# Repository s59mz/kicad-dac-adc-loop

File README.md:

# dac_adc_pmod
PMOD PCB module with LTC2627 (I2C-DAC) and LTC2402 (SPI-ADC) loopback

Schematic:
[dac_adc_pmod.pdf](dac_adc_pmod.pdf)

BOM:
[dac_adc_pmod.csv](dac_adc_pmod.csv)

Gerbers:
[gerbers.zip](https://github.com/s59mz/kicad-dac-adc-loop/raw/main/gerbers.zip)

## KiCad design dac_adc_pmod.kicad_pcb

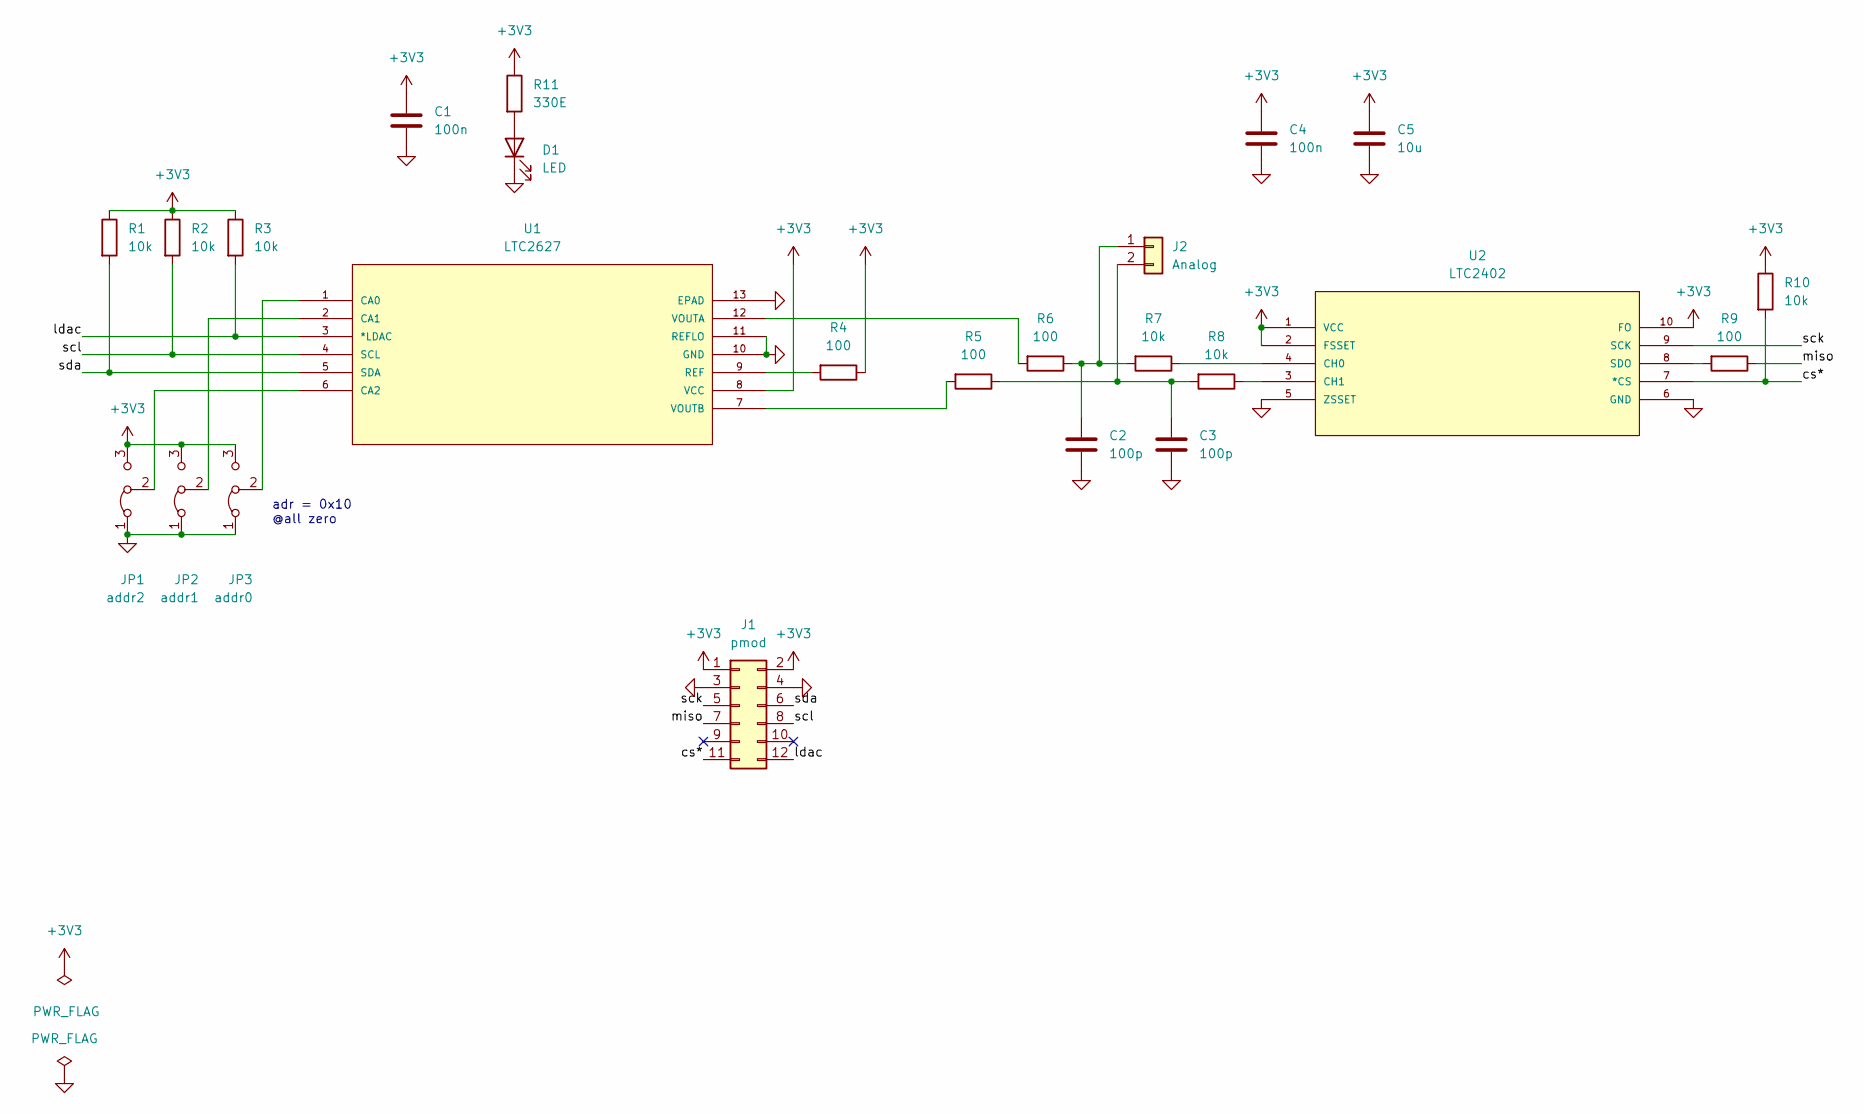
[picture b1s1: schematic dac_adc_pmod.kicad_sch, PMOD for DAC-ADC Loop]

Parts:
C1, C4: 100n; C_0603_1608Metric_Pad1.08x0.95mm_HandSolder
C2, C3: 100p; C_0603_1608Metric_Pad1.08x0.95mm_HandSolder
C5: 10u; C_0603_1608Metric_Pad1.08x0.95mm_HandSolder
D1: LED; LED_0603_1608Metric_Pad1.05x0.95mm_HandSolder
J1: pmod; PinHeader_2x06_P2.54mm_Horizontal
J2: Analog; PinHeader_1x02_P2.54mm_Vertical
JP1: addr2; PinHeader_1x03_P2.54mm_Vertical
JP2: addr1; PinHeader_1x03_P2.54mm_Vertical
JP3: addr0; PinHeader_1x03_P2.54mm_Vertical
R1, R2, R3, R7, R8, R10: 10k; R_0603_1608Metric_Pad0.98x0.95mm_HandSolder
R4, R5, R6, R9: 100; R_0603_1608Metric_Pad0.98x0.95mm_HandSolder
R11: 330E; R_0603_1608Metric_Pad0.98x0.95mm_HandSolder
U1: LTC2627; DFN-12; MANUFACTURER_PART_NUMBER ltc2627cde
U2: LTC2402; MSOP-10; MANUFACTURER_PART_NUMBER ltc2402ims

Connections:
+3V3: C1.1, C4.1, C5.1, J1.1, J1.2, JP1.3 (B), JP2.3 (B), JP3.3 (B), R1.1, R2.1, R3.1, R4.1, R10.1, R11.1, U1.8 (VCC), U2.1 (VCC), U2.2 (FSSET), U2.10 (FO)
/cs*: J1.11, R10.2, U2.7 (*CS)
/ldac: J1.12, R3.2, U1.3 (*LDAC)
/miso: J1.7, R9.1
/sck: J1.5, U2.9 (SCK)
/scl: J1.8, R2.2, U1.4 (SCL)
/sda: J1.6, R1.2, U1.5 (SDA)
GND: C1.2, C2.2, C3.2, C4.2, C5.2, D1.1 (K), J1.3, J1.4, JP1.1 (A), JP2.1 (A), JP3.1 (A), U1.10 (GND), U1.11 (REFLO), U1.13 (EPAD), U2.5 (ZSSET), U2.6 (GND)
unnamed: C2.1, J2.1, R6.1, R7.2
unnamed: C3.1, J2.2, R5.1, R8.2
unnamed: D1.2 (A), R11.2
unnamed: JP1.2 (C), U1.6 (CA2)
unnamed: JP2.2 (C), U1.2 (CA1)
unnamed: JP3.2 (C), U1.1 (CA0)
unnamed: R4.2, U1.9 (REF)
unnamed: R5.2, U1.7 (VOUTB)
unnamed: R6.2, U1.12 (VOUTA)
unnamed: R7.1, U2.4 (CH0)
unnamed: R8.1, U2.3 (CH1)
unnamed: R9.2, U2.8 (SDO)

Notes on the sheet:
adr = 0x10 @all zero

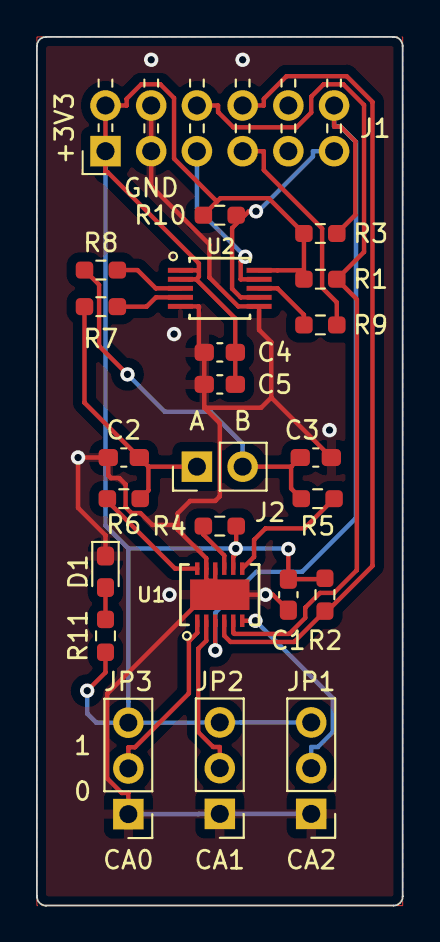
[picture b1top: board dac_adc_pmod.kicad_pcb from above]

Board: 2 copper layers, 20.3 x 48.3 mm, 24 parts (0 on the bottom side), 20 nets.

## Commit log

2023-03-08 fixed block capacitor
2024-08-11 add screenshots
